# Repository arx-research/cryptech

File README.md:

# CrypTech Repos

This repository is a collection of git submodules associated with the [CrypTech](https://cryptech.is) project.

To use on a fresh repository run:
`git clone --recurse-submodules -j8 https://github.com/arx-project/cryptech.git`

Or on an already cloned repo:
`git submodule update --init --recursive`

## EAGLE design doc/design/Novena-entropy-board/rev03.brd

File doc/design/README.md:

design documentation
====================

This repo contains a number of documents used during development of
various parts the Cryptech design. Note that the directory contains
source files (for example in OmniGraffle, Open Document file formats) as
well as final documents (normally in PFF file format).

* Alpha_board_drawing
  A drawing/diagram that shows the functional components and their
  functional connectivities for the Cryptech Alpha board being
  developed. The drawing is not formal schematics for the Alpha board.

* Novena-entropy-board
  Sub directory with schematics as well as layout with silk screen for
  the Cryptech Noise board designed to be used as external entropy
  source on the Novena.

* alpha_board_config
  Configuration file for setting up the I/Os and functionality of the
  STM32 microcontroller on the Alpha board. The config file is used by
  the tool [STM32CubeMX][http://www.st.com/web/catalog/tools/FM147/CL1794/SC961/SS1743/PF259242?sc=microxplorer] from ST Microelectronics.

* application-aware-signing
  A drawing that shows a proposed mechanism with data and command flows
  for doing application based (application aware) signing.

* fpga_estimates
  A document that tracks the FPGA resources and performance of the
  different Cryptech cores in different FPGA technologies. The document
  also includes estimates for cores not yet designed or completed. The
  purpose of the document is to provide estimates of FPGA devices needed
  to implement different use cases.

* hsm-board
  A high level functional diagram of the Cryptech HSM board that shows
  the major functional blocks. Used during development of the Alpha
  board to see what components are needed to realise the functionality
  of the blocks. The Alpha_board_drawing is the concrete functional
  realisation of this diagram.

* hsm-keys
  A document that includes diagrams that shows proposed mechanisms for
  handling keys including managament, protection and migration of
  wrapped keys.

* novena-memory-map
  This document contains information about the memory map of the
  Cryptech FPGA design with the specific memory maps of each core as
  well as how the cores are addressed and accessed from SW via different
  interfaces.

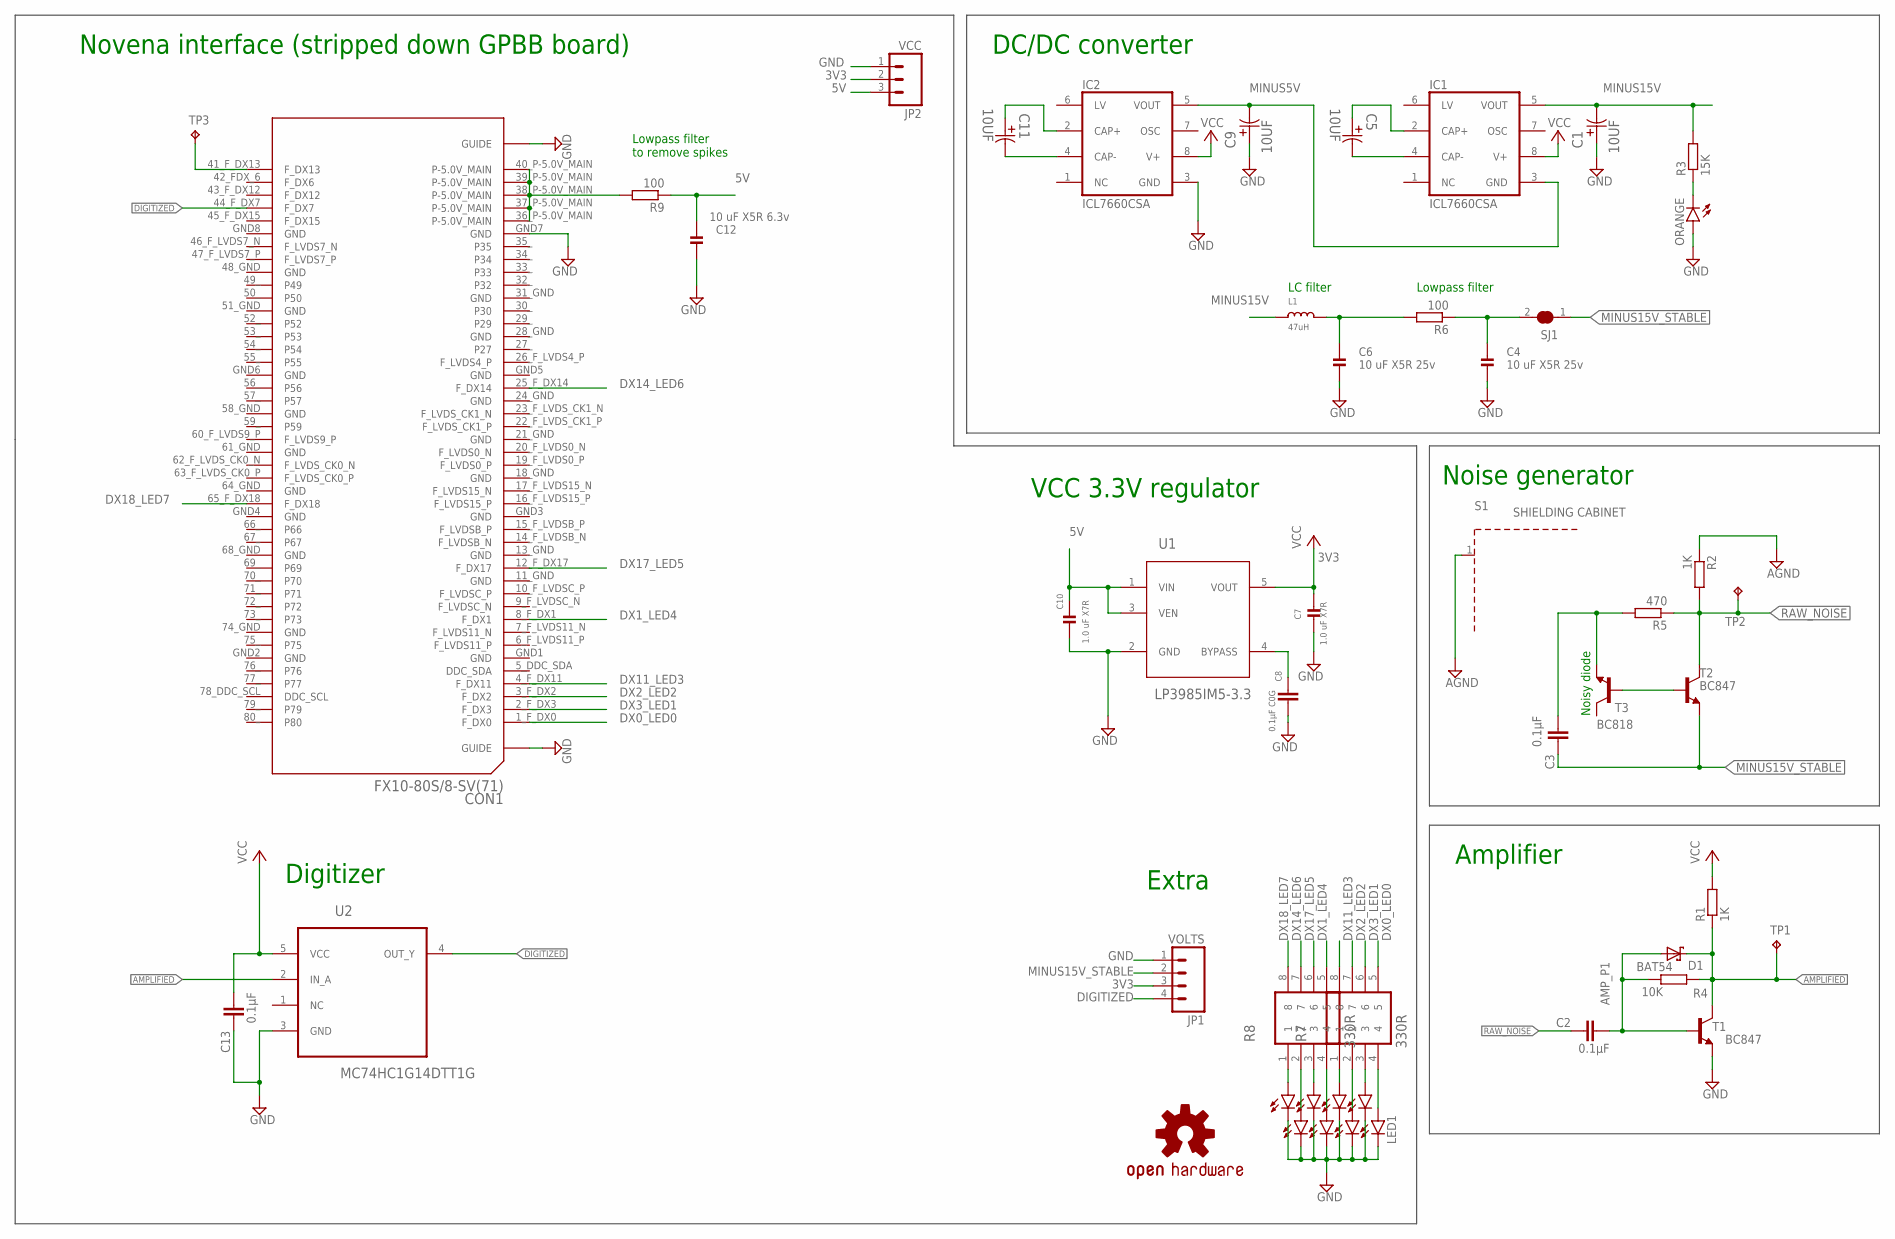
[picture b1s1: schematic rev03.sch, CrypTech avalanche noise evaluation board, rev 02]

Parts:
C1, C5, C9, C11: 10UF; CAPAE530X610N
C2, C3, C13: 0.1µF; C0603
C4, C6: 10 uF X5R 25v; _0805
C7, C10: 1.0 uF X7R; 0805
C8: 0.1µF C0G; C0603
C12: 10 uF X5R 6.3v; 0805
CON1: FX10-80S/8-SV(71); FX10A-80P/8-SV(71)
D1: BAT54; SOT23
IC1, IC2: ICL7660CSA; SO08
JP1: VOLTS; 1X04_LOCK
JP2: VCC; 1X03_LOCK
L1: 47uH; _0805
LED1, LED2, LED3, LED4, LED5, LED6, LED7, LED8: LED0603; LED-0603
LOGO1: OSHW-LOGOL; OSHW-LOGO-L
ORANGE: LED0603; LED-0603
R1, R2: 1K; R0603
R3: 15K; R0603
R4: 10K; R0603
R5: 470; R0603
R6, R9: 100; R0603
R7, R8: 330R; RESCAXE80P320X160X60-8N
S1: SHIELDING CABINET; WE-SHC_36103205
SJ1: SOLDERJUMPER_CLOSED; SOLDERJUMPER_CLOSEDWIRE
T1, T2: BC847; SOT23
T3: BC818; SOT23-BEC
TP1, TP2: TPB1,27; B1,27
TP3: TP_NEAT; TP_NEAT_0032
U1: LP3985IM5-3.3; SOT95P300X120-5N
U2: MC74HC1G14DTT1G; SOT95P275X110-5N

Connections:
3V3: C7.1, C13.2, JP1.3, JP2.2, R1.2, U1.5 (VOUT), U2.5 (VCC)
5V: C10.1, C12.1, IC1.8 (V+), IC2.8 (V+), JP2.3, R9.1, U1.1 (VIN), U1.3 (VEN)
AGND: C13.1, R2.1, S1.1, T1.2 (E), U2.3 (GND)
AMPLIFIED: D1.3 (C), R1.1, R4.2, T1.3 (C), TP1.TP, U2.2 (IN_A)
AMP_P1: C2.2, D1.1 (A), R4.1, T1.1 (B)
DIGITIZED: CON1.44_F_DX7 (F_DX7), JP1.4, U2.4 (OUT_Y)
DX0_LED0: CON1.1_F_DX0 (F_DX0), R7.5
DX1_LED4: CON1.8_F_DX1 (F_DX1), R8.5
DX2_LED2: CON1.3_F_DX2 (F_DX2), R7.7
DX3_LED1: CON1.2_F_DX3 (F_DX3), R7.6
DX11_LED3: CON1.4_F_DX11 (F_DX11), R7.8
DX13: CON1.41_F_DX13 (F_DX13), TP3.TP
DX14_LED6: CON1.25_F_DX14 (F_DX14), R8.7
DX17_LED5: CON1.12_F_DX17 (F_DX17), R8.6
DX18_LED7: CON1.65_F_DX18 (F_DX18), R8.8
GND: C1.1, C4.2, C6.2, C7.2, C8.1, C9.1, C10.2, C12.2, CON1.GND1 (GND), CON1.GND2 (GND), CON1.GND3 (GND), CON1.GND4 (GND), CON1.GND5 (GND), CON1.GND6 (GND), CON1.GND7 (GND), CON1.GND8 (GND), CON1.GUIDE@L (GUIDE), CON1.GUIDE@R (GUIDE), IC2.3 (GND), JP1.1, JP2.1, LED1.C, LED2.C, LED3.C, LED4.C, LED5.C, LED6.C, LED7.C, LED8.C, ORANGE.A, U1.2 (GND)
MINUS5V: C9.2, IC1.3 (GND), IC2.5 (VOUT)
MINUS15V: C1.2, IC1.5 (VOUT), L1.1, R3.2
MINUS15V_STABLE: C3.1, JP1.2, SJ1.1, T2.2 (E)
unnamed: C5.2, IC1.4 (CAP-)
unnamed: C11.2, IC2.4 (CAP-)
unnamed: C11.1, IC2.2 (CAP+)
unnamed: LED1.A, R7.4
unnamed: LED2.A, R7.3
unnamed: C4.1, R6.1, SJ1.2
unnamed: ORANGE.C, R3.1
unnamed: C8.2, U1.4 (BYPASS)
unnamed: C5.1, IC1.2 (CAP+)
unnamed: C6.1, L1.2, R6.2
unnamed: LED3.A, R7.2
unnamed: LED4.A, R7.1
unnamed: LED5.A, R8.4
unnamed: LED6.A, R8.3
unnamed: LED7.A, R8.2
unnamed: LED8.A, R8.1
NOISE_IN: C3.2, R5.2, T3.E
NOISE_OUT: T2.1 (B), T3.B
P-5.0V_MAIN: CON1.36_P-5.0V_MAIN (P-5.0V_MAIN), CON1.37_P-5.0V_MAIN (P-5.0V_MAIN), CON1.38_P-5.0V_MAIN (P-5.0V_MAIN), CON1.39_P-5.0V_MAIN (P-5.0V_MAIN), CON1.40_P-5.0V_MAIN (P-5.0V_MAIN), R9.2
RAW_NOISE: C2.1, R2.2, R5.1, T2.3 (C), TP2.TP

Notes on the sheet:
Novena interface (stripped down GPBB board)
DC/DC converter
Noise generator
Amplifier
Extra
Noisy diode
Digitizer
VCC 3.3V regulator
Lowpass filter to remove spikes
Lowpass filter
LC filter

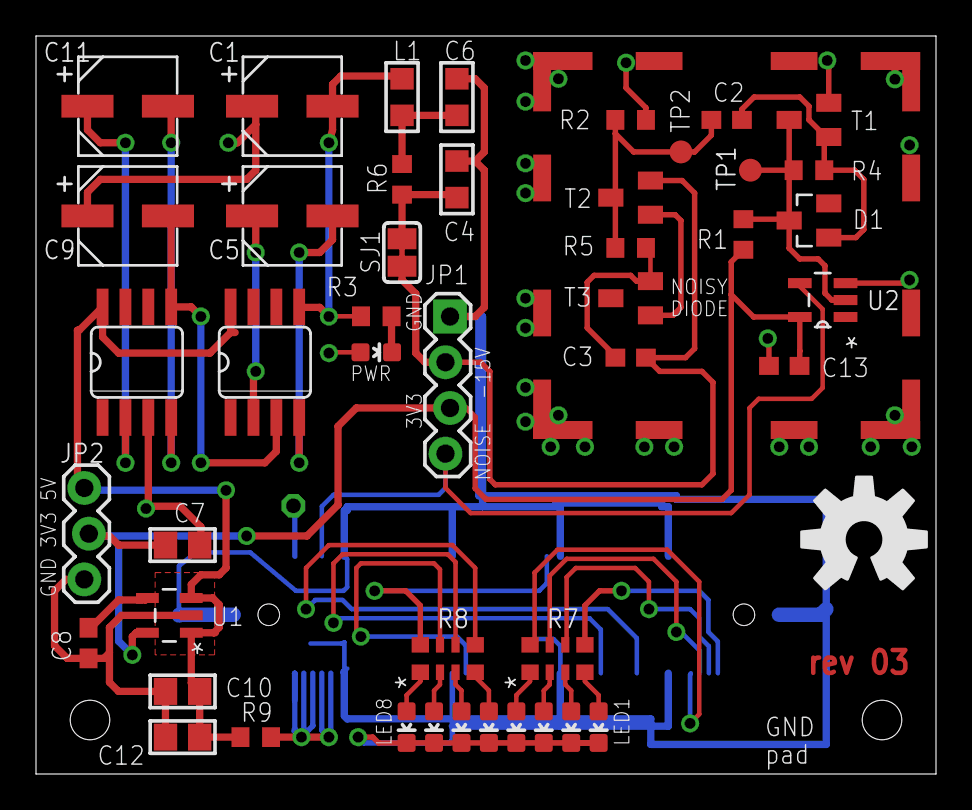
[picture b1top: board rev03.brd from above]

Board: 2 copper layers, 50.0 x 41.0 mm, 49 parts (1 on the bottom side), 39 nets.

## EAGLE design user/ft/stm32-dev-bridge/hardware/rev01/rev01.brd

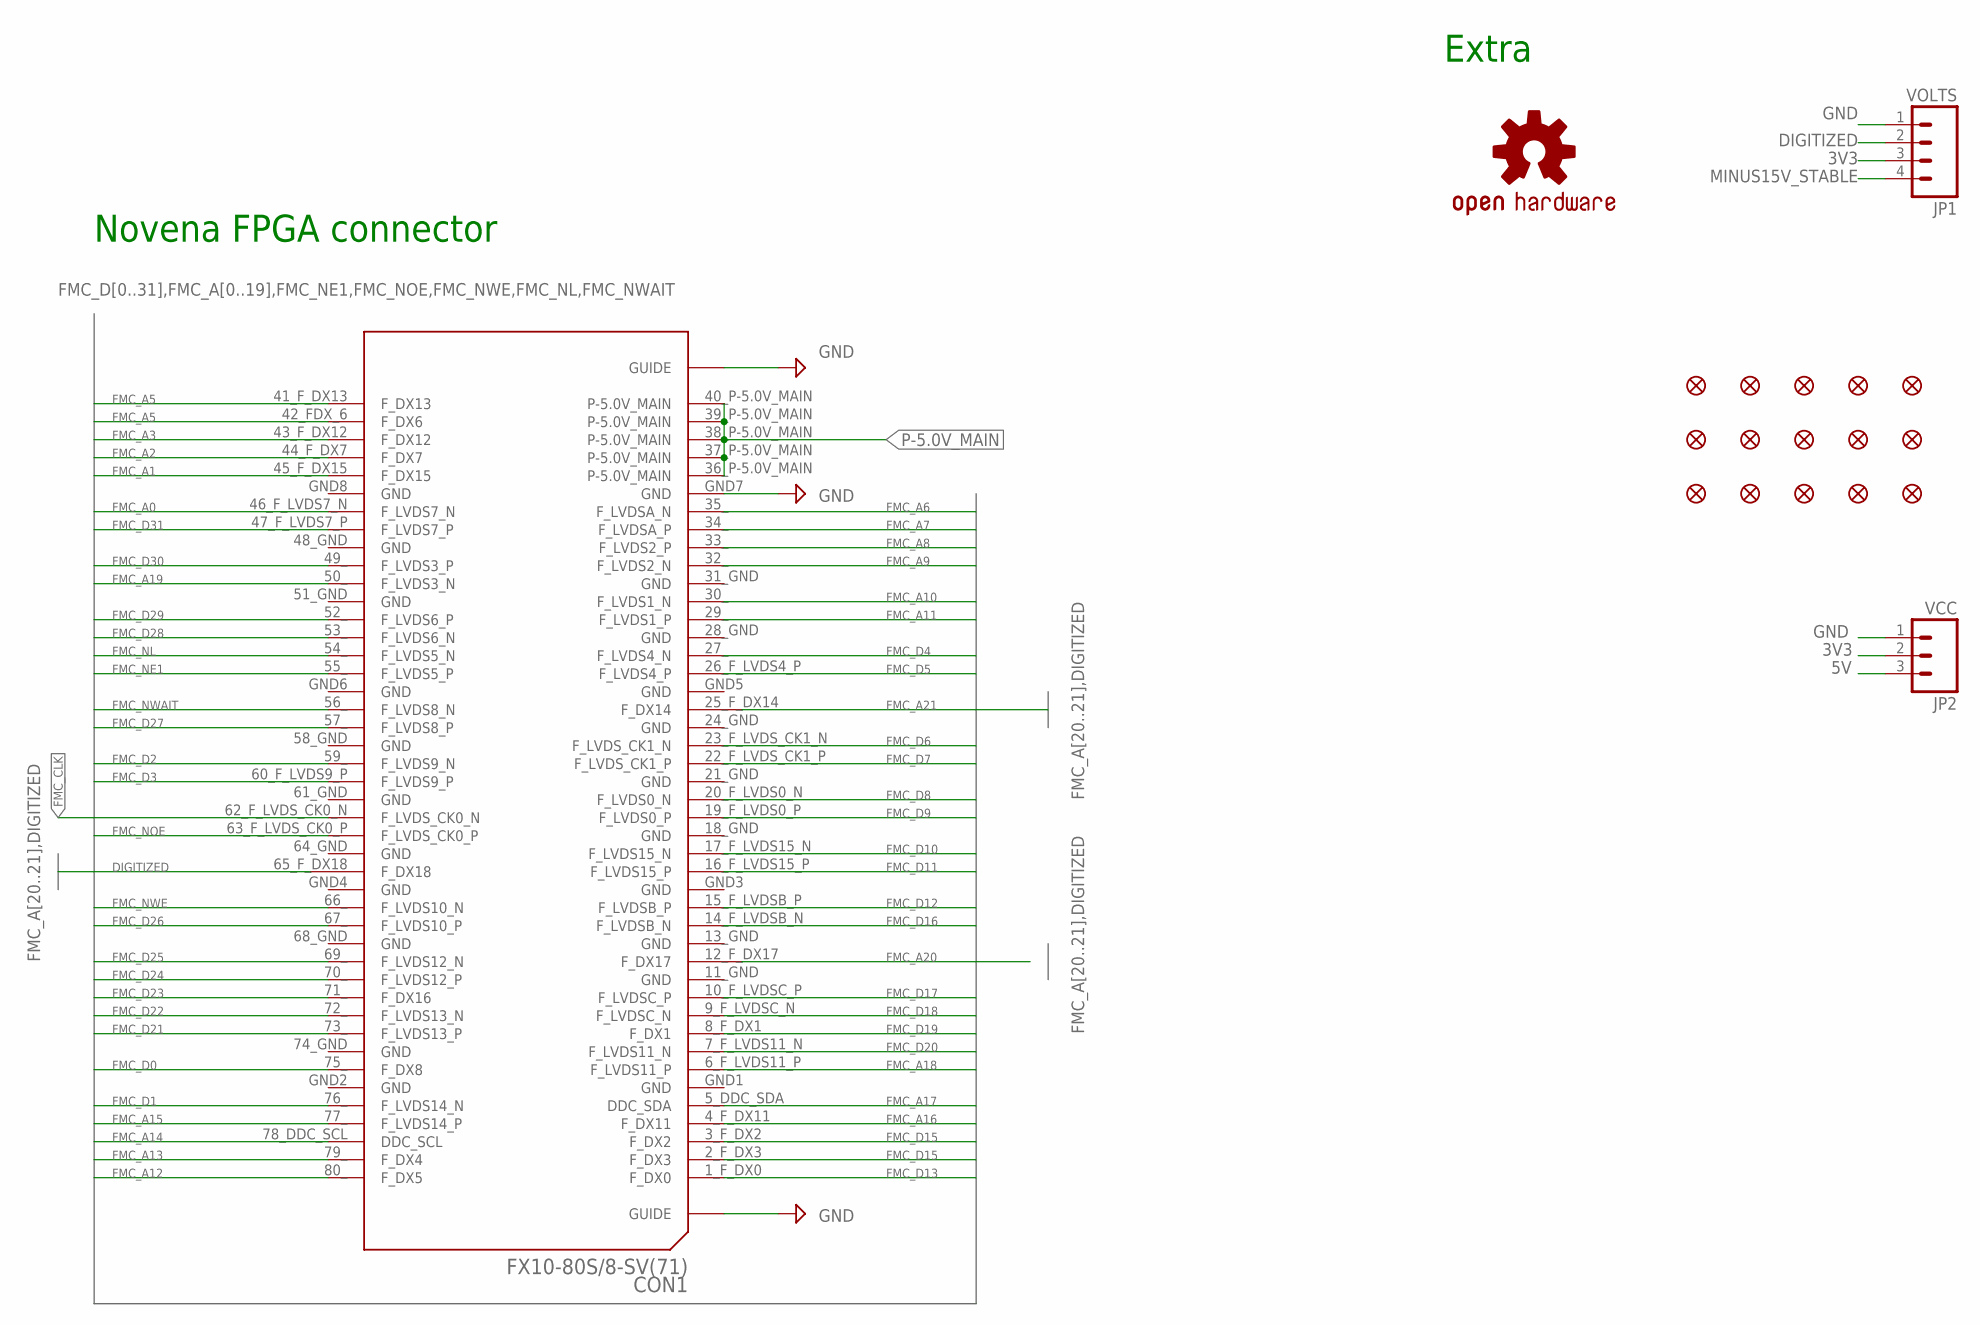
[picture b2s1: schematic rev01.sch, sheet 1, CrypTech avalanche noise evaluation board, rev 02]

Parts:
CON1: FX10-80S/8-SV(71); FX10A-80P/8-SV(71)
FID1, FID2, FID3, FID4, FID5, FID6, FID7, FID8, FID9, FID10, FID11, FID12, FID13, FID14, FID15: FIDUCIAL1X2; FIDUCIAL-1X2
JP1: VOLTS; 1X04_LOCK
JP2: VCC; 1X03_LOCK
LOGO1: OSHW-LOGOL-COPPER; OSHW-LOGO-L_COPPER

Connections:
3V3: JP1.3, JP2.2; also elsewhere on the board
5V: JP2.3; also elsewhere on the board
DIGITIZED: CON1.65_F_DX18 (F_DX18), JP1.2; also elsewhere on the board
FMC_A0: CON1.46_F_LVDS7_N (F_LVDS7_N); also elsewhere on the board
FMC_A1: CON1.45_F_DX15 (F_DX15); also elsewhere on the board
FMC_A2: CON1.44_F_DX7 (F_DX7); also elsewhere on the board
FMC_A3: CON1.43_F_DX12 (F_DX12); also elsewhere on the board
FMC_A4: CON1.42_FDX_6 (F_DX6); also elsewhere on the board
FMC_A5: CON1.41_F_DX13 (F_DX13); also elsewhere on the board
FMC_A6: CON1.35_ (F_LVDSA_N); also elsewhere on the board
FMC_A7: CON1.34_ (F_LVDSA_P); also elsewhere on the board
FMC_A8: CON1.33_ (F_LVDS2_P); also elsewhere on the board
FMC_A9: CON1.32_ (F_LVDS2_N); also elsewhere on the board
FMC_A10: CON1.30_ (F_LVDS1_N); also elsewhere on the board
FMC_A11: CON1.29_ (F_LVDS1_P); also elsewhere on the board
FMC_A12: CON1.80_ (F_DX5); also elsewhere on the board
FMC_A13: CON1.79_ (F_DX4); also elsewhere on the board
FMC_A14: CON1.78_DDC_SCL (DDC_SCL); also elsewhere on the board
FMC_A15: CON1.77_ (F_LVDS14_P); also elsewhere on the board
FMC_A16: CON1.4_F_DX11 (F_DX11); also elsewhere on the board
FMC_A17: CON1.5_DDC_SDA (DDC_SDA); also elsewhere on the board
FMC_A18: CON1.6_F_LVDS11_P (F_LVDS11_P); also elsewhere on the board
FMC_A19: CON1.50_ (F_LVDS3_N); also elsewhere on the board
FMC_A20: CON1.12_F_DX17 (F_DX17); also elsewhere on the board
FMC_A21: CON1.25_F_DX14 (F_DX14); also elsewhere on the board
FMC_CLK: CON1.62_F_LVDS_CK0_N (F_LVDS_CK0_N); also elsewhere on the board
FMC_D0: CON1.75_ (F_DX8); also elsewhere on the board
FMC_D1: CON1.76_ (F_LVDS14_N); also elsewhere on the board
FMC_D2: CON1.59_ (F_LVDS9_N); also elsewhere on the board
FMC_D3: CON1.60_F_LVDS9_P (F_LVDS9_P); also elsewhere on the board
FMC_D4: CON1.27_ (F_LVDS4_N); also elsewhere on the board
FMC_D5: CON1.26_F_LVDS4_P (F_LVDS4_P); also elsewhere on the board
FMC_D6: CON1.23_F_LVDS_CK1_N (F_LVDS_CK1_N); also elsewhere on the board
FMC_D7: CON1.22_F_LVDS_CK1_P (F_LVDS_CK1_P); also elsewhere on the board
FMC_D8: CON1.20_F_LVDS0_N (F_LVDS0_N); also elsewhere on the board
FMC_D9: CON1.19_F_LVDS0_P (F_LVDS0_P); also elsewhere on the board
FMC_D10: CON1.17_F_LVDS15_N (F_LVDS15_N); also elsewhere on the board
FMC_D11: CON1.16_F_LVDS15_P (F_LVDS15_P); also elsewhere on the board
FMC_D12: CON1.15_F_LVDSB_P (F_LVDSB_P); also elsewhere on the board
FMC_D13: CON1.1_F_DX0 (F_DX0); also elsewhere on the board
FMC_D14: CON1.2_F_DX3 (F_DX3); also elsewhere on the board
FMC_D15: CON1.3_F_DX2 (F_DX2); also elsewhere on the board
FMC_D16: CON1.14_F_LVDSB_N (F_LVDSB_N); also elsewhere on the board
FMC_D17: CON1.10_F_LVDSC_P (F_LVDSC_P); also elsewhere on the board
FMC_D18: CON1.9_F_LVDSC_N (F_LVDSC_N); also elsewhere on the board
FMC_D19: CON1.8_F_DX1 (F_DX1); also elsewhere on the board
FMC_D20: CON1.7_F_LVDS11_N (F_LVDS11_N); also elsewhere on the board
FMC_D21: CON1.73_ (F_LVDS13_P); also elsewhere on the board
FMC_D22: CON1.72_ (F_LVDS13_N); also elsewhere on the board
FMC_D23: CON1.71_ (F_DX16); also elsewhere on the board
FMC_D24: CON1.70_ (F_LVDS12_P); also elsewhere on the board
FMC_D25: CON1.69_ (F_LVDS12_N); also elsewhere on the board
FMC_D26: CON1.67_ (F_LVDS10_P); also elsewhere on the board
FMC_D27: CON1.57_ (F_LVDS8_P); also elsewhere on the board
FMC_D28: CON1.53_ (F_LVDS6_N); also elsewhere on the board
FMC_D29: CON1.52_ (F_LVDS6_P); also elsewhere on the board
FMC_D30: CON1.49_ (F_LVDS3_P); also elsewhere on the board
FMC_D31: CON1.47_F_LVDS7_P (F_LVDS7_P); also elsewhere on the board
FMC_NE1: CON1.55_ (F_LVDS5_P); also elsewhere on the board
FMC_NL: CON1.54_ (F_LVDS5_N); also elsewhere on the board
FMC_NOE: CON1.63_F_LVDS_CK0_P (F_LVDS_CK0_P); also elsewhere on the board
FMC_NWAIT: CON1.56_ (F_LVDS8_N); also elsewhere on the board
FMC_NWE: CON1.66_ (F_LVDS10_N); also elsewhere on the board
GND: CON1.GND1 (GND), CON1.GND2 (GND), CON1.GND3 (GND), CON1.GND4 (GND), CON1.GND5 (GND), CON1.GND6 (GND), CON1.GND7 (GND), CON1.GND8 (GND), CON1.GUIDE@L (GUIDE), CON1.GUIDE@R (GUIDE), JP1.1, JP2.1; also elsewhere on the board
MINUS15V_STABLE: JP1.4; also elsewhere on the board
P-5.0V_MAIN: CON1.36_P-5.0V_MAIN (P-5.0V_MAIN), CON1.37_P-5.0V_MAIN (P-5.0V_MAIN), CON1.38_P-5.0V_MAIN (P-5.0V_MAIN), CON1.39_P-5.0V_MAIN (P-5.0V_MAIN), CON1.40_P-5.0V_MAIN (P-5.0V_MAIN); also elsewhere on the board

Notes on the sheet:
Novena FPGA connector
Extra

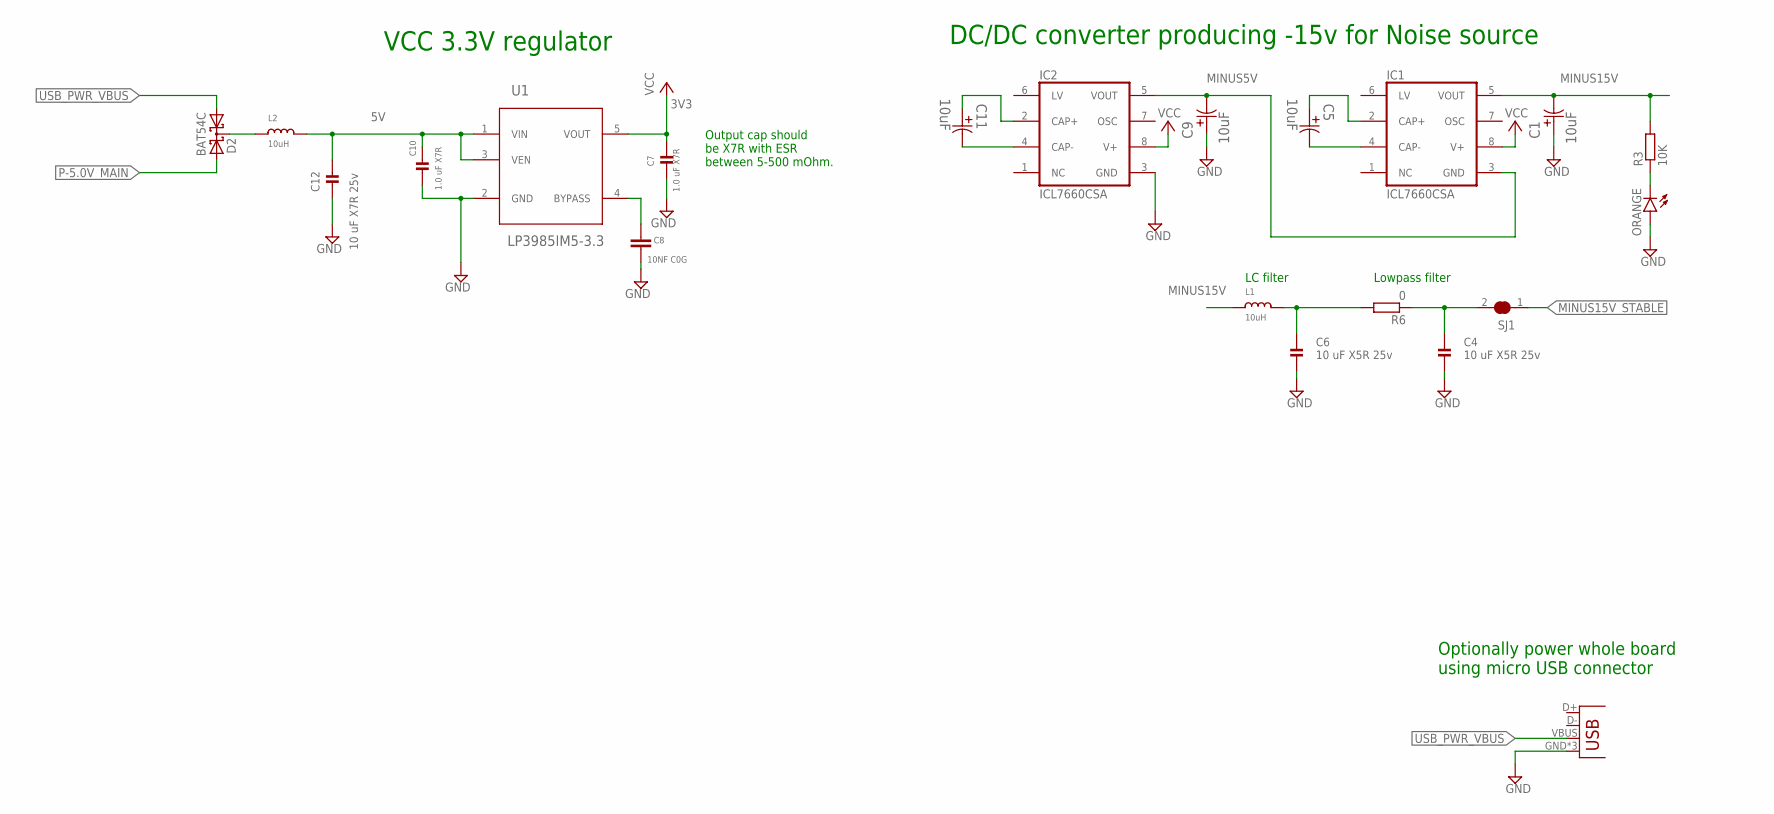
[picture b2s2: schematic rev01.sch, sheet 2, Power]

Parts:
C1, C5, C9, C11: 10uF; CAPAE530X610N_BIG_PADS
C4, C6: 10 uF X5R 25v; _0805
C7, C10: 1.0 uF X7R; 0805
C8: 10NF C0G; C0603
C12: 10 uF X7R 25v; 0805
D2: BAT54C; SOT23
IC1, IC2: ICL7660CSA; SO08
L1, L2: 10uH; _0805
ORANGE: LEDAMBER0603; LED-0603
R3: 10K; R0603
R6: 0; R0603
SJ1: SOLDERJUMPER_CLOSED; SOLDERJUMPER_CLOSEDWIRE@1
U1: LP3985IM5-3.3; SOT95P300X120-5N
USB_PWR: USB-MICROB

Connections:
3V3: C7.1, U1.5 (VOUT); also elsewhere on the board
5V: C10.1, C12.1, IC1.8 (V+), IC2.8 (V+), L2.2, U1.1 (VIN), U1.3 (VEN); also elsewhere on the board
GND: C1.1, C4.2, C6.2, C7.2, C8.1, C9.1, C10.2, C12.2, IC2.3 (GND), ORANGE.A, U1.2 (GND), USB_PWR.GND, USB_PWR.MT1 (GND), USB_PWR.MT2 (GND); also elsewhere on the board
MINUS5V: C9.2, IC1.3 (GND), IC2.5 (VOUT)
MINUS15V: C1.2, IC1.5 (VOUT), L1.1, R3.2
MINUS15V_STABLE: SJ1.1; also elsewhere on the board
unnamed: C5.2, IC1.4 (CAP-)
unnamed: C11.2, IC2.4 (CAP-)
unnamed: C11.1, IC2.2 (CAP+)
unnamed: C4.1, R6.1, SJ1.2
unnamed: ORANGE.C, R3.1
unnamed: C8.2, U1.4 (BYPASS)
unnamed: C5.1, IC1.2 (CAP+)
unnamed: C6.1, L1.2, R6.2
unnamed: D2.3 (CC), L2.1
P-5.0V_MAIN: D2.2 (A2); also elsewhere on the board
USB_PWR_VBUS: D2.1 (A1), USB_PWR.VBUS

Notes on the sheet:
VCC 3.3V regulator
DC/DC converter producing -15v for Noise source
Lowpass filter
LC filter
Optionally power whole board using micro USB connector
Output cap should be X7R with ESR between 5-500 mOhm.

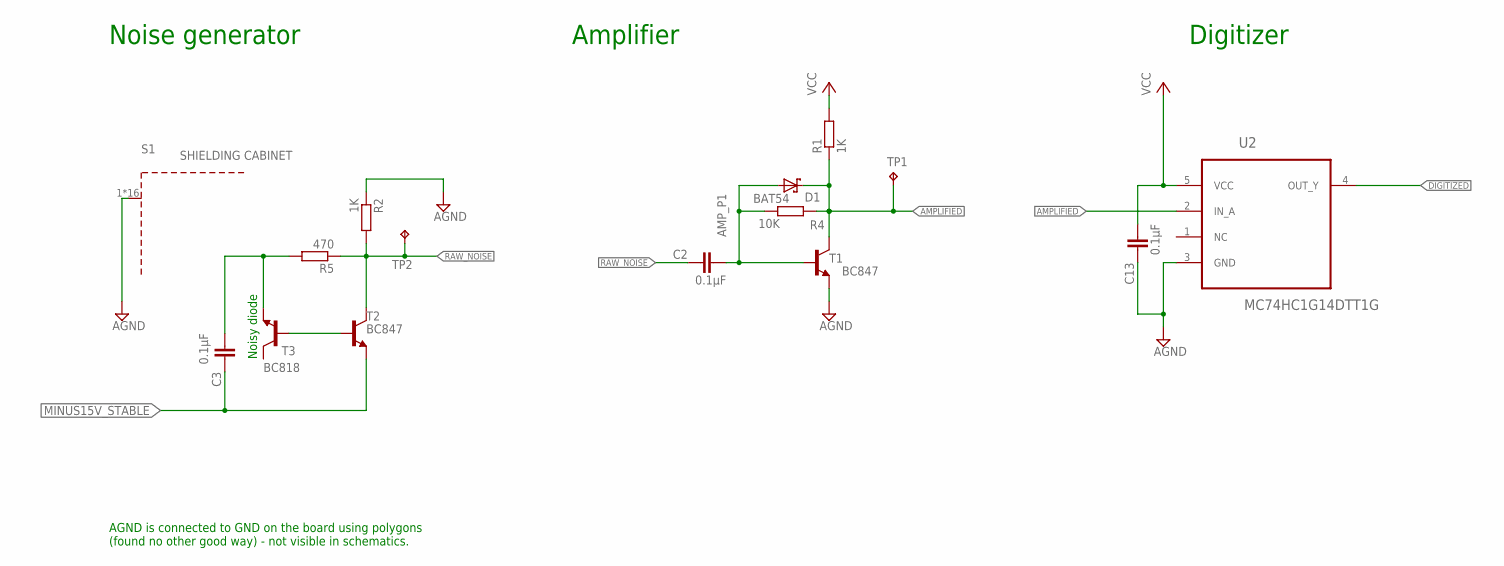
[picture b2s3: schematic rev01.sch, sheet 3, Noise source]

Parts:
C2, C3, C13: 0.1µF; C0603
D1: BAT54; SOT23
R1, R2: 1K; R0603
R4: 10K; R0603
R5: 470; R0603
S1: SHIELDING CABINET; WE-SHC_36103205_NO_CREAM
T1, T2: BC847; SOT23
T3: BC818; SOT23-BEC
TP1, TP2: TPB1,27; B1,27
U2: MC74HC1G14DTT1G; SOT95P275X110-5N

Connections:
3V3: C13.2, R1.2, U2.5 (VCC); also elsewhere on the board
AGND: C13.1, R2.1, S1.1, S1.2, S1.3, S1.4, S1.5, S1.6, S1.7, S1.8, S1.9, S1.10, S1.11, S1.12, S1.13, S1.14, S1.15, S1.16, T1.2 (E), U2.3 (GND)
AMPLIFIED: D1.3 (C), R1.1, R4.2, T1.3 (C), TP1.TP, U2.2 (IN_A)
AMP_P1: C2.2, D1.1 (A), R4.1, T1.1 (B)
DIGITIZED: U2.4 (OUT_Y); also elsewhere on the board
MINUS15V_STABLE: C3.1, T2.2 (E); also elsewhere on the board
NOISE_IN: C3.2, R5.2, T3.E
NOISE_OUT: T2.1 (B), T3.B
RAW_NOISE: C2.1, R2.2, R5.1, T2.3 (C), TP2.TP

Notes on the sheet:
Digitizer
Noise generator
Noisy diode
Amplifier
AGND is connected to GND on the board using polygons (found no other good way) - not visible in schematics.

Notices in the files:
core/platform/alpha/ucf/alpha_fmc.ucf:
Copyright (c) 2016, NORDUnet A/S All rights reserved.
user/ft/stm32-avalanche-noise/src/cc20rng/main.c:
Copyright (c) 2014, 2015, 2016 NORDUnet A/S
All rights reserved.
parts and their libraries:
SparkFun-LED: Licensing: Creative Commons ShareAlike 4.0 International - https://creativecommons.org/licenses/by-sa/4.0
microbuilder: This work is placed in the public domain, and may be freely used for commercial and non-commercial work with the following conditions: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
